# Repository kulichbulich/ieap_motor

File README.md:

# 4-Channel Motor Controller with ESP32
## Parts

### ESP32
Pin assigment https://github.com/atomic14/esp32-s3-pinouts/blob/main/README.md?utm_source=chatgpt.com

### Motor-driver module
Datasheet: https://www.analog.com/media/en/technical-documentation/data-sheets/TMC2209-BOB_datasheet_rev1.00.pdf
Motor module (KiCAD files): https://www.analog.com/media/en/evaluation-documentation/evaluation-design-files/TMC2209-BOB_Rev1.0.zip

### DC/DC converter
LT8610: https://www.analog.com/media/en/technical-documentation/data-sheets/lt8610.pdf
+5V Power supply

+5V Power supply

### Polyswitch
https://cz.mouser.com/ProductDetail/Littelfuse/MINISMDC150F-24-2?qs=F6FIpiMdEVZ%2Fp37J%2FDHAxA%3D%3D

# Enclosure

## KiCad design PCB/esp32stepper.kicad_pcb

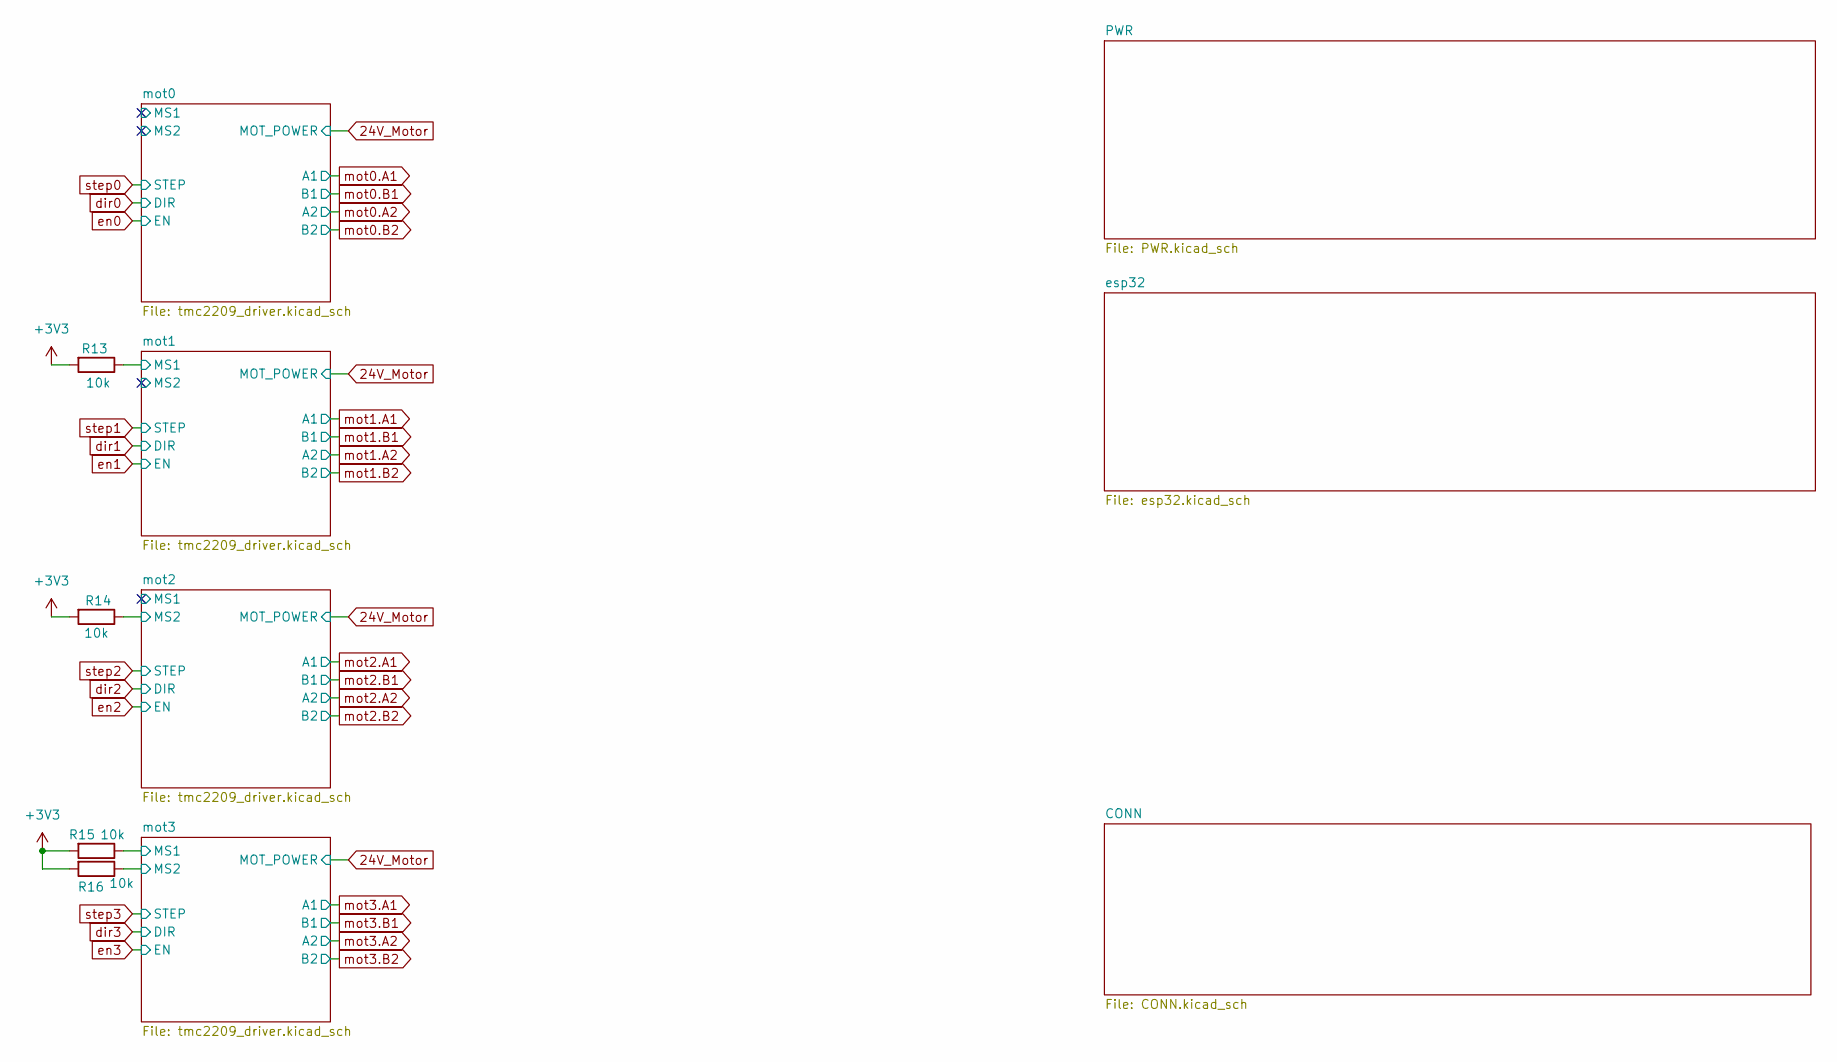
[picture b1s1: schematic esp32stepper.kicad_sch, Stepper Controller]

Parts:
R13, R14, R15, R16: 10k; R_0603_1608Metric_Pad0.98x0.95mm_HandSolder

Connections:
+3V3: R13.2, R14.2, R15.2, R16.2; also elsewhere on the board
/mot1/MS1: R13.1; also elsewhere on the board
/mot2/MS2: R14.1; also elsewhere on the board
/mot3/MS1: R15.1; also elsewhere on the board
/mot3/MS2: R16.1; also elsewhere on the board

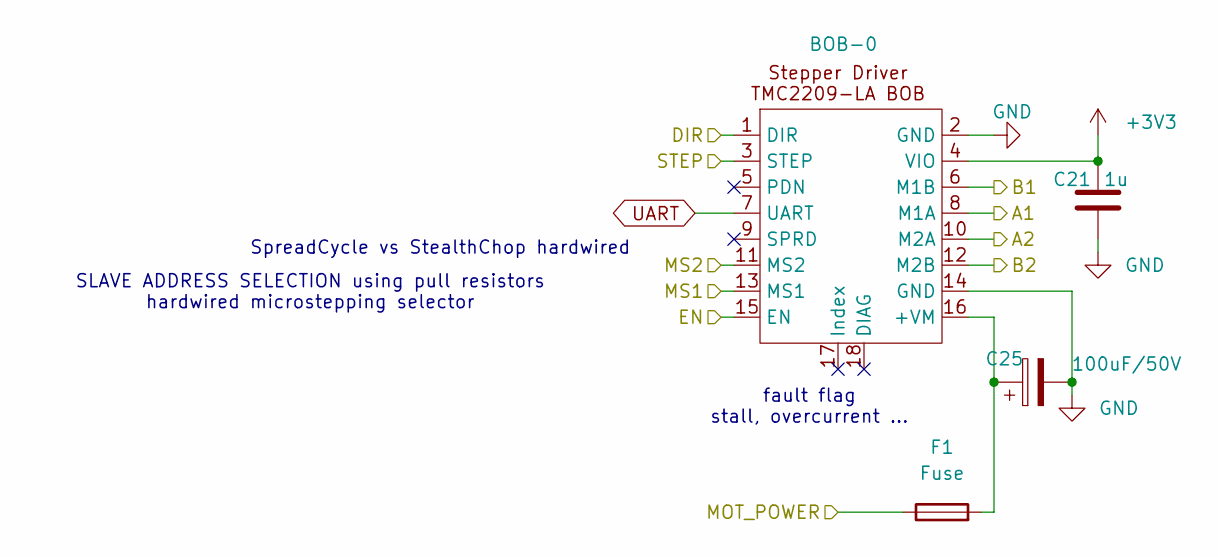
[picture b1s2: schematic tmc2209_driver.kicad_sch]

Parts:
BOB-0: TMC2209_SilentStepStick
C21: 1u; C_0603_1608Metric_Pad1.08x0.95mm_HandSolder
C25: 100uF/50V; CP_Elec_8x10.5
F1: Fuse; Fuse_1812_4532Metric_Pad1.30x3.40mm_HandSolder

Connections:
24V_Motor: F1.1; also elsewhere on the board
+3V3: BOB-0.4 (VIO), C21.2; also elsewhere on the board
/mot0/MS1: BOB-0.13 (MS1)
/mot0/MS2: BOB-0.11 (MS2)
GND: BOB-0.2 (GND), BOB-0.14 (GND), C21.1, C25.2; also elsewhere on the board
unnamed: BOB-0.16 (+VM), C25.1, F1.2
UART: BOB-0.7 (UART); also elsewhere on the board
dir0: BOB-0.1 (DIR); also elsewhere on the board
en0: BOB-0.15 (EN); also elsewhere on the board
mot0.A1: BOB-0.8 (M1A); also elsewhere on the board
mot0.A2: BOB-0.10 (M2A); also elsewhere on the board
mot0.B1: BOB-0.6 (M1B); also elsewhere on the board
mot0.B2: BOB-0.12 (M2B); also elsewhere on the board
step0: BOB-0.3 (STEP); also elsewhere on the board

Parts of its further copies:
C22, C23, C24: 1u; C_0603_1608Metric_Pad1.08x0.95mm_HandSolder
C26, C27, C28: 100uF/50V; CP_Elec_8x10.5
F3, F4, F5: Fuse; Fuse_1812_4532Metric_Pad1.30x3.40mm_HandSolder

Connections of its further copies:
24V_Motor: F3.1, F4.1, F5.1; also elsewhere on the board
+3V3: C22.2, C23.2, C24.2; also elsewhere on the board
GND: C22.1, C23.1, C24.1, C26.2, C27.2, C28.2; also elsewhere on the board
unnamed 17: C26.1, F3.2; also elsewhere on the board
unnamed 18: C27.1, F4.2; also elsewhere on the board
unnamed 19: C28.1, F5.2; also elsewhere on the board

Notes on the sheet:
fault flag stall, overcurrent ...
SLAVE ADDRESS SELECTION using pull resistors hardwired microstepping selector
SpreadCycle vs StealthChop hardwired

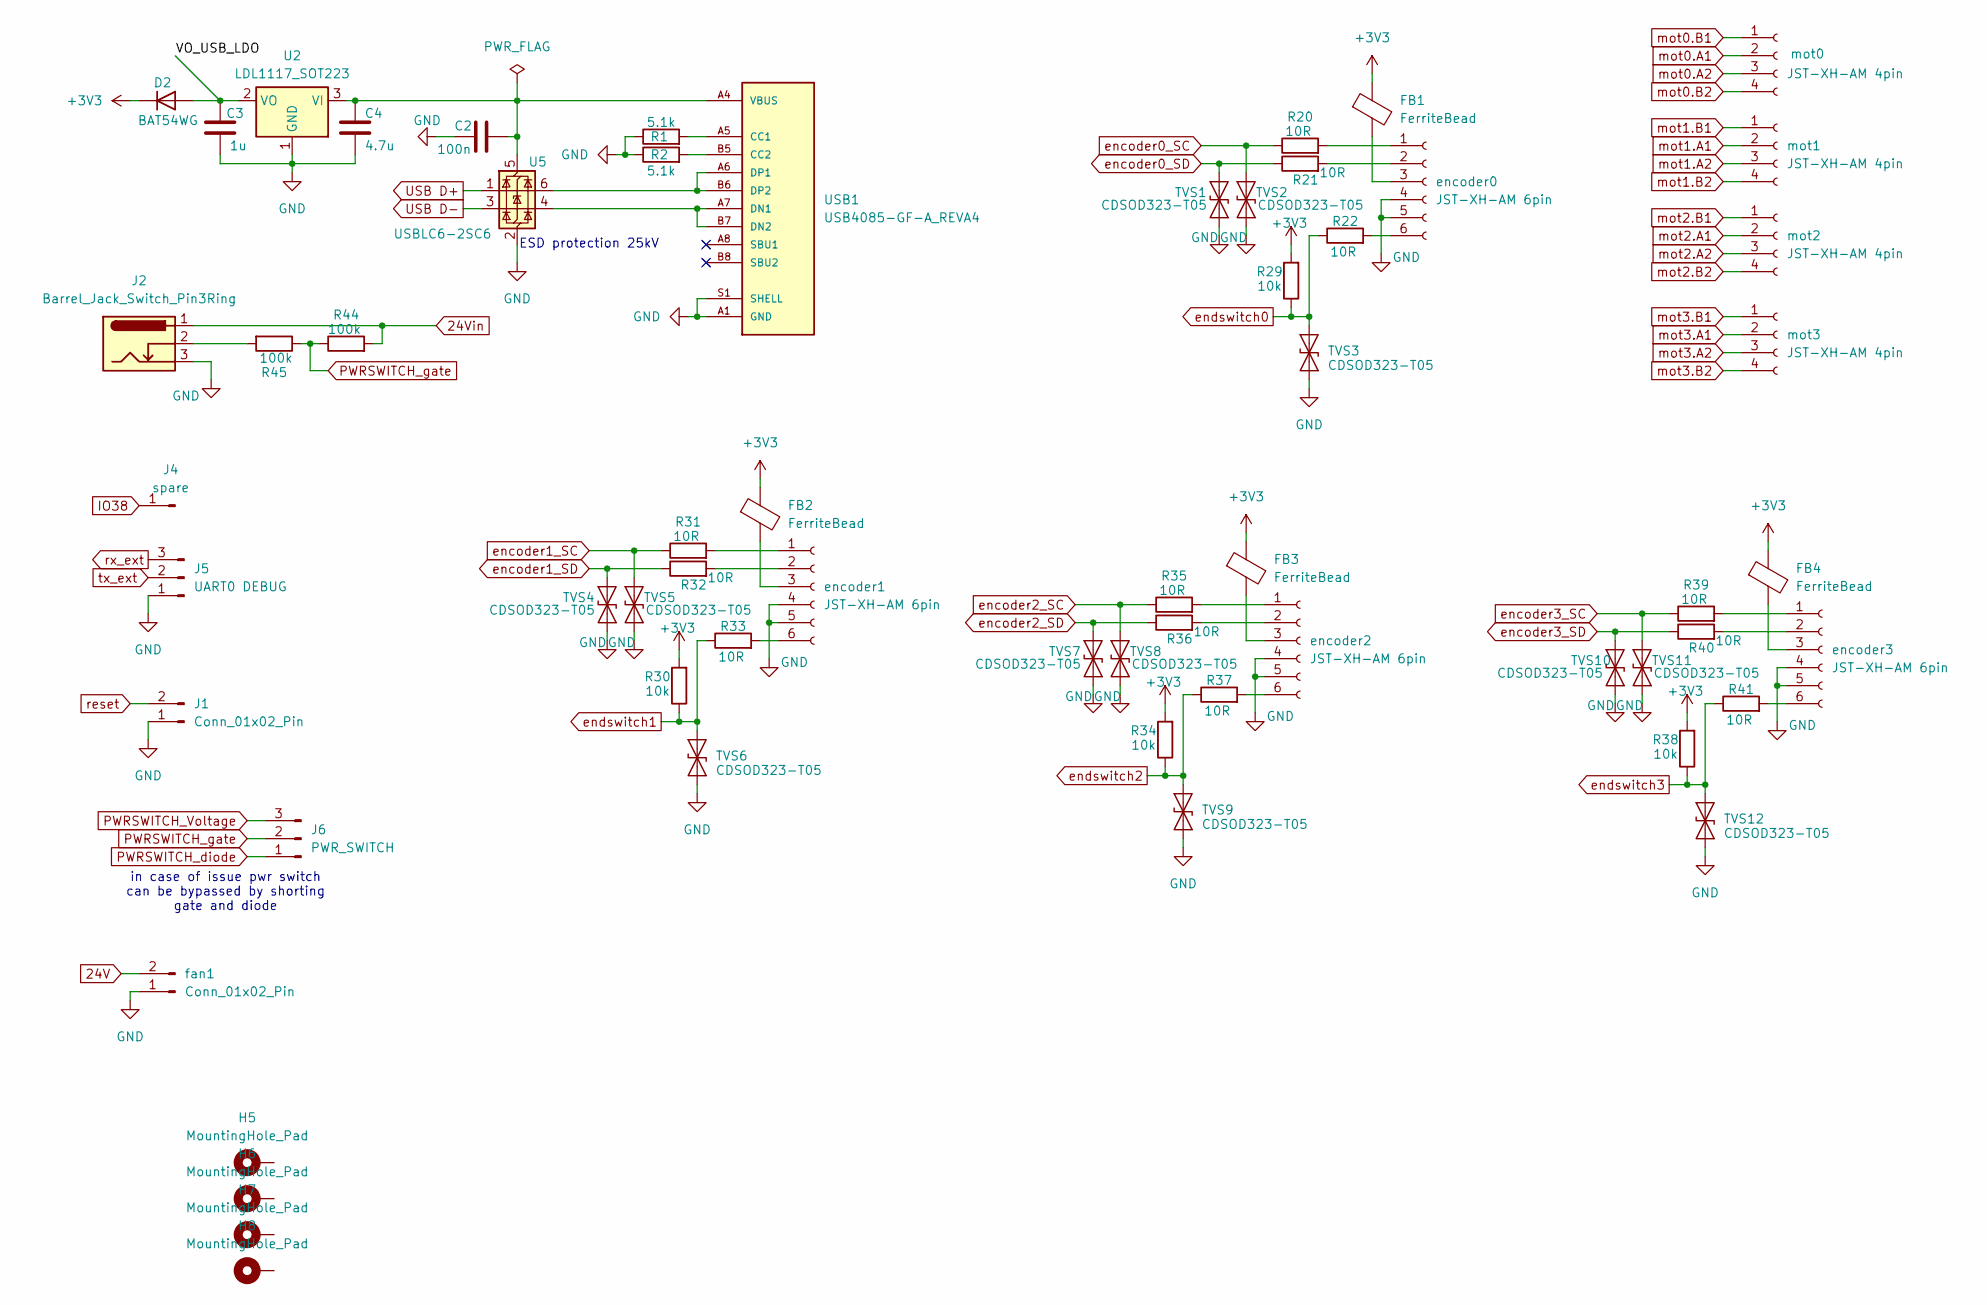
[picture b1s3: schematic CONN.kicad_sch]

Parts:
C2: 100n; C_0603_1608Metric_Pad1.08x0.95mm_HandSolder
C3: 1u; C_0603_1608Metric_Pad1.08x0.95mm_HandSolder
C4: 4.7u; C_0603_1608Metric_Pad1.08x0.95mm_HandSolder
D2: BAT54WG; SOT-323_SC-70_Handsoldering
FB1, FB2, FB3, FB4: FerriteBead; L_0603_1608Metric_Pad1.05x0.95mm_HandSolder
H5, H6, H7, H8: MountingHole_Pad; MountingHole_3.2mm_M3_DIN965_Pad
J1: Conn_01x02_Pin; PinHeader_1x02_P2.54mm_Vertical
J2: Barrel_Jack_Switch_Pin3Ring; BarrelJack_Wuerth_6941xx301002
J4: spare; PinHeader_1x01_P2.54mm_Vertical
J5: UART0 DEBUG; PinHeader_1x03_P2.54mm_Vertical
J6: PWR_SWITCH; PinHeader_1x03_P2.54mm_Vertical
R1, R2: 5.1k; R_0603_1608Metric_Pad0.98x0.95mm_HandSolder
R20, R21, R22, R31, R32, R33, R35, R36, R37, R39, R40, R41: 10R; R_0603_1608Metric_Pad0.98x0.95mm_HandSolder
R29, R30, R34, R38: 10k; R_0603_1608Metric_Pad0.98x0.95mm_HandSolder
R44, R45: 100k; R_0603_1608Metric_Pad0.98x0.95mm_HandSolder
TVS1, TVS2, TVS3, TVS4, TVS5, TVS6, TVS7, TVS8, TVS9, TVS10, TVS11, TVS12: CDSOD323-T05; D_SOD-323
U2: LDL1117_SOT223; SOT-223-3_TabPin2
U5: USBLC6-2SC6; SOT-23-6
USB1: USB4085-GF-A_REVA4; GCT_USB4085-GF-A_REVA4; PARTREV A4
encoder0, encoder1, encoder2, encoder3: JST-XH-AM 6pin; JST_XH_B6B-XH-AM_1x06_P2.50mm_Vertical
fan1: Conn_01x02_Pin; PinHeader_1x02_P2.54mm_Vertical
mot0, mot1, mot2, mot3: JST-XH-AM 4pin; JST_XH_B4B-XH-AM_1x04_P2.50mm_Vertical

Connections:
24V: fan1.2; also elsewhere on the board
24Vin: J2.1, R44.2; also elsewhere on the board
+3V3: D2.1 (K), FB1.1, FB2.1, FB3.1, FB4.1, R29.2, R30.2, R34.2, R38.2; also elsewhere on the board
/CONN/VO_USB_LDO: C3.1, D2.2 (A), U2.2 (VO)
GND: C2.1, C3.2, C4.2, J1.1, J2.3, J5.1, R1.1, R2.1, TVS1.1 (A1), TVS2.1 (A1), TVS3.1 (A1), TVS4.1 (A1), TVS5.1 (A1), TVS6.1 (A1), TVS7.1 (A1), TVS8.1 (A1), TVS9.1 (A1), TVS10.1 (A1), TVS11.1 (A1), TVS12.1 (A1), U2.1 (GND), U5.2 (GND), USB1.A1 (GND), USB1.A12 (GND), USB1.B1 (GND), USB1.B12 (GND), USB1.S1 (SHELL), USB1.S2 (SHELL), USB1.S3 (SHELL), USB1.S4 (SHELL), encoder0.4, encoder0.5, encoder1.4, encoder1.5, encoder2.4, encoder2.5, encoder3.4, encoder3.5, fan1.1; also elsewhere on the board
IO38: J4.1 (Pin_1_1); also elsewhere on the board
unnamed: J2.2, R45.2
unnamed: R1.2, USB1.A5 (CC1)
unnamed: R2.2, USB1.B5 (CC2)
unnamed: U5.4 (I/O2), USB1.A7 (DN1), USB1.B7 (DN2)
unnamed: U5.6 (I/O1), USB1.A6 (DP1), USB1.B6 (DP2)
unnamed: R20.2, encoder0.1
unnamed: R21.2, encoder0.2
unnamed: FB1.2, encoder0.3
unnamed: R22.2, encoder0.6
unnamed: R31.2, encoder1.1
unnamed: R32.2, encoder1.2
unnamed: FB2.2, encoder1.3
unnamed: R33.2, encoder1.6
unnamed: R35.2, encoder2.1
unnamed: R36.2, encoder2.2
unnamed: FB3.2, encoder2.3
unnamed: R37.2, encoder2.6
unnamed: R39.2, encoder3.1
unnamed: R40.2, encoder3.2
unnamed: FB4.2, encoder3.3
unnamed: R41.2, encoder3.6
PWRSWITCH_Voltage: J6.3; also elsewhere on the board
PWRSWITCH_diode: J6.1; also elsewhere on the board
PWRSWITCH_gate: J6.2, R44.1, R45.1; also elsewhere on the board
USB D+: U5.1 (I/O1); also elsewhere on the board
USB D-: U5.3 (I/O2); also elsewhere on the board
VBUS: C2.2, C4.1, U2.3 (VI), U5.5 (VBUS), USB1.A4 (VBUS), USB1.A9 (VBUS), USB1.B4 (VBUS), USB1.B9 (VBUS)
encoder0_SC: R20.1, TVS2.2 (A2); also elsewhere on the board
encoder0_SD: R21.1, TVS1.2 (A2); also elsewhere on the board
encoder1_SC: R31.1, TVS5.2 (A2); also elsewhere on the board
encoder1_SD: R32.1, TVS4.2 (A2); also elsewhere on the board
encoder2_SC: R35.1, TVS8.2 (A2); also elsewhere on the board
encoder2_SD: R36.1, TVS7.2 (A2); also elsewhere on the board
encoder3_SC: R39.1, TVS11.2 (A2); also elsewhere on the board
encoder3_SD: R40.1, TVS10.2 (A2); also elsewhere on the board
endswitch0: R22.1, R29.1, TVS3.2 (A2); also elsewhere on the board
endswitch1: R30.1, R33.1, TVS6.2 (A2); also elsewhere on the board
endswitch2: R34.1, R37.1, TVS9.2 (A2); also elsewhere on the board
endswitch3: R38.1, R41.1, TVS12.2 (A2); also elsewhere on the board
mot0.A1: mot0.2; also elsewhere on the board
mot0.A2: mot0.3; also elsewhere on the board
mot0.B1: mot0.1; also elsewhere on the board
mot0.B2: mot0.4; also elsewhere on the board
mot1.A1: mot1.2; also elsewhere on the board
mot1.A2: mot1.3; also elsewhere on the board
mot1.B1: mot1.1; also elsewhere on the board
mot1.B2: mot1.4; also elsewhere on the board
mot2.A1: mot2.2; also elsewhere on the board
mot2.A2: mot2.3; also elsewhere on the board
mot2.B1: mot2.1; also elsewhere on the board
mot2.B2: mot2.4; also elsewhere on the board
mot3.A1: mot3.2; also elsewhere on the board
mot3.A2: mot3.3; also elsewhere on the board
mot3.B1: mot3.1; also elsewhere on the board
mot3.B2: mot3.4; also elsewhere on the board
reset: J1.2; also elsewhere on the board
rx_ext: J5.3; also elsewhere on the board
tx_ext: J5.2; also elsewhere on the board

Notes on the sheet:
in case of issue pwr switch can be bypassed by shorting gate and diode
ESD protection 25kV

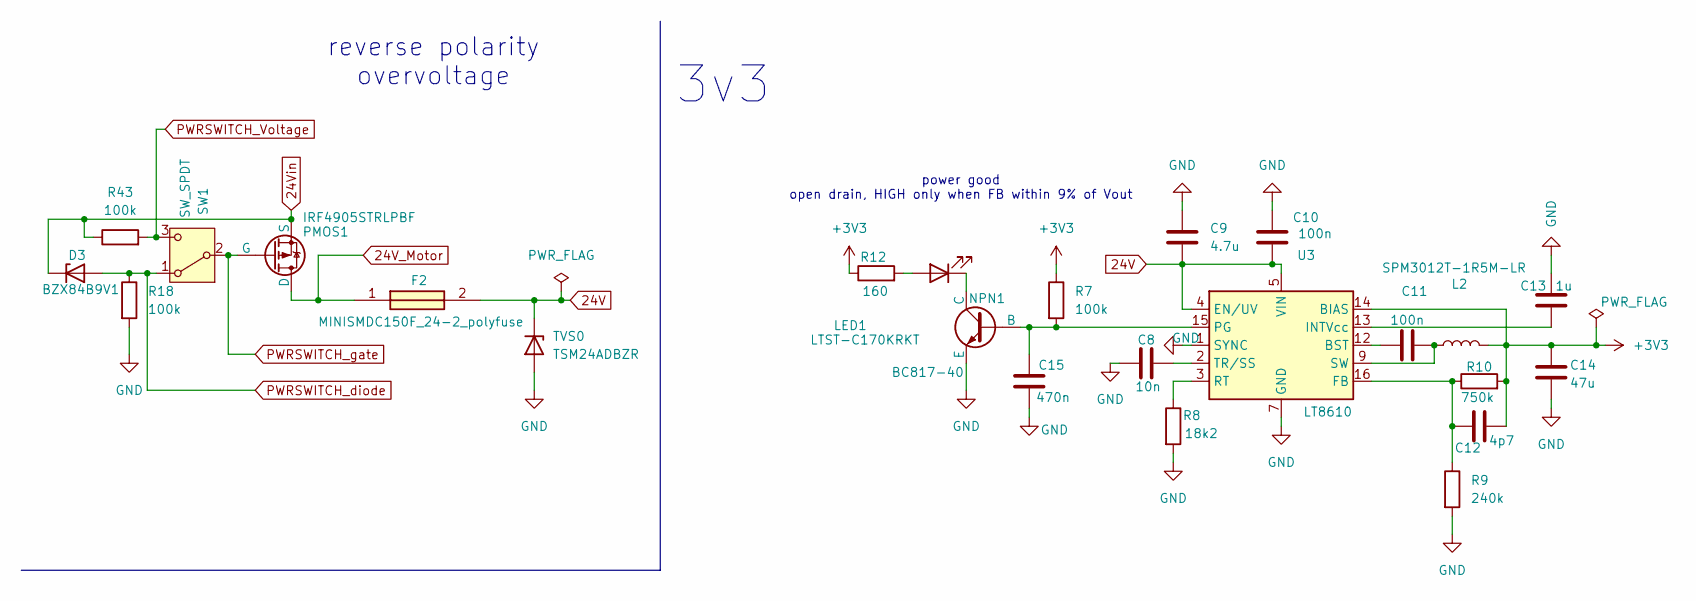
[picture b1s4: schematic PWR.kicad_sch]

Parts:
C8: 10n; C_0603_1608Metric_Pad1.08x0.95mm_HandSolder
C9: 4.7u; C_0805_2012Metric_Pad1.18x1.45mm_HandSolder
C10, C11: 100n; C_0603_1608Metric_Pad1.08x0.95mm_HandSolder
C12: 4p7; C_0603_1608Metric_Pad1.08x0.95mm_HandSolder
C13: 1u; C_0603_1608Metric_Pad1.08x0.95mm_HandSolder
C14: 47u; C_0603_1608Metric_Pad1.08x0.95mm_HandSolder
C15: 470n; C_0603_1608Metric_Pad1.08x0.95mm_HandSolder
D3: BZX84B9V1; SOT-23
F2: MINISMDC150F_24-2_polyfuse; polyfuse; Mouser Part Number 650-MINISMDC150F/24
L2: SPM3012T-1R5M-LR; SPM3010-3020
LED1: LTST-C170KRKT; LED_0805_2012Metric_Pad1.15x1.40mm_HandSolder
NPN1: BC817-40; TSOT-23_HandSoldering
PMOS1: IRF4905STRLPBF; TO-263-2
R7, R18, R43: 100k; R_0603_1608Metric_Pad0.98x0.95mm_HandSolder
R8: 18k2; R_0603_1608Metric_Pad0.98x0.95mm_HandSolder
R9: 240k; R_0603_1608Metric_Pad0.98x0.95mm_HandSolder
R10: 750k; R_0603_1608Metric_Pad0.98x0.95mm_HandSolder
R12: 160; R_0603_1608Metric_Pad0.98x0.95mm_HandSolder
SW1: SW_SPDT
TVS0: TSM24ADBZR; TSOT-23
U3: LT8610; MSOP-16-1EP_3x4.039mm_P0.5mm_EP1.651x2.845mm_ThermalVias

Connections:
24V: C9.2, C10.2, F2.2, TVS0.1 (K), U3.4 (EN/UV), U3.5 (VIN), U3.6 (VIN); also elsewhere on the board
24V_Motor: F2.1, PMOS1.1 (D); also elsewhere on the board
24Vin: D3.1 (K), PMOS1.3 (S), R43.1; also elsewhere on the board
+3V3: C12.1, C14.1, L2.2, R7.1, R10.2, R12.1, U3.14 (BIAS); also elsewhere on the board
GND: C8.1, C9.1, C10.1, C13.2, C14.2, C15.1, NPN1.3 (E), R8.2, R9.2, R18.2, TVS0.2 (A), U3.1 (SYNC), U3.7 (GND), U3.8 (GND), U3.17 (GND); also elsewhere on the board
unnamed: C11.2, L2.1, U3.9 (SW), U3.10 (SW), U3.11 (SW)
unnamed: LED1.2 (A), R12.2
unnamed: LED1.1 (K), NPN1.1 (C)
unnamed: C15.2, NPN1.2 (B), R7.2, U3.15 (PG)
unnamed: C11.1, U3.12 (BST)
unnamed: C12.2, R9.1, R10.1, U3.16 (FB)
unnamed: C13.1, U3.13 (INTVcc)
unnamed: R8.1, U3.3 (RT)
unnamed: C8.2, U3.2 (TR/SS)
PWRSWITCH_Voltage: R43.2, SW1.3 (C); also elsewhere on the board
PWRSWITCH_diode: D3.2 (A), R18.1, SW1.1 (A); also elsewhere on the board
PWRSWITCH_gate: PMOS1.2 (G), SW1.2 (B); also elsewhere on the board

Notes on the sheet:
power good open drain, HIGH only when FB within 9% of Vout
reverse polarity overvoltage
3v3

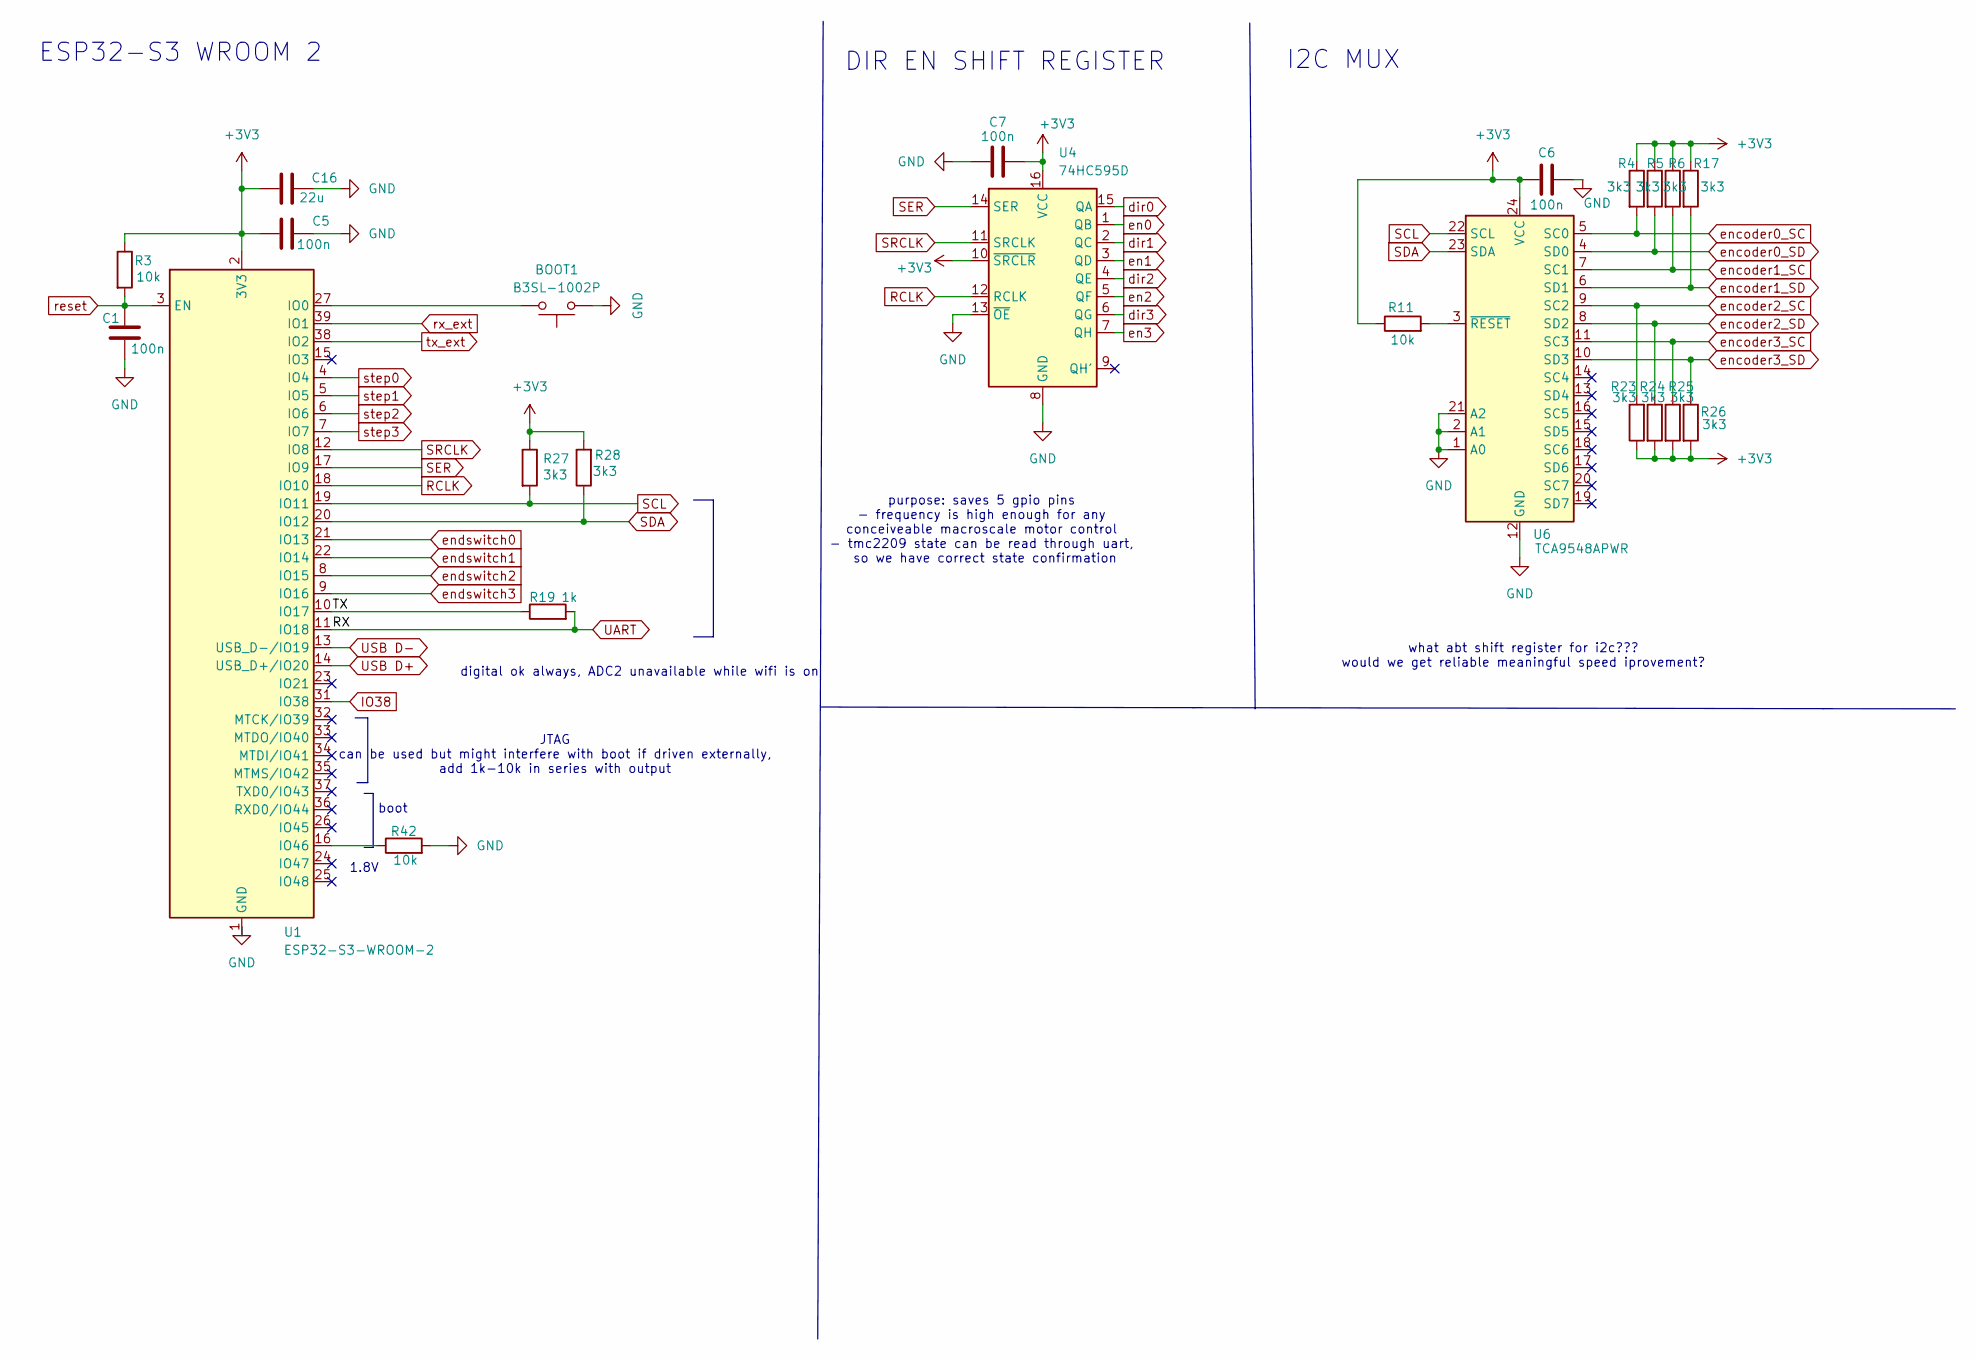
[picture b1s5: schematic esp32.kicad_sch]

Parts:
BOOT1: B3SL-1002P; SW_SPST_B3SL-1002P
C1, C5, C6, C7: 100n; C_0603_1608Metric_Pad1.08x0.95mm_HandSolder
C16: 22u; C_0603_1608Metric_Pad1.08x0.95mm_HandSolder
R3, R11, R42: 10k; R_0603_1608Metric_Pad0.98x0.95mm_HandSolder
R4, R5, R6, R17, R23, R24, R25, R26, R27, R28: 3k3; R_0603_1608Metric_Pad0.98x0.95mm_HandSolder
R19: 1k; R_0603_1608Metric_Pad0.98x0.95mm_HandSolder
U1: ESP32-S3-WROOM-2
U4: 74HC595D; SOIC-16_3.9x9.9mm_P1.27mm
U6: TCA9548APWR; TSSOP-24_4.4x7.8mm_P0.65mm

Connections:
+3V3: C5.1, C6.1, C7.2, C16.2, R3.1, R4.1, R5.1, R6.1, R11.1, R17.1, R23.1, R24.2, R25.2, R26.2, R27.1, R28.2, U1.2 (3V3), U4.10 (~SRCLR), U4.16 (VCC), U6.24 (VCC); also elsewhere on the board
/esp32/TX: R19.1, U1.10 (IO17)
GND: BOOT1.1, C1.2, C5.2, C6.2, C7.1, C16.1, R42.2, U1.1 (GND), U1.40 (GND), U1.41 (GND), U4.8 (GND), U4.13 (~OE), U6.1 (A0), U6.2 (A1), U6.12 (GND), U6.21 (A2); also elsewhere on the board
IO38: U1.31 (IO38); also elsewhere on the board
unnamed: BOOT1.2, U1.27 (IO0)
unnamed: R42.1, U1.16 (IO46)
unnamed: R11.2, U6.3 (~RESET)
RCLK: U1.18 (IO10), U4.12 (RCLK)
SCL: R27.2, U1.19 (IO11), U6.22 (SCL)
SDA: R28.1, U1.20 (IO12), U6.23 (SDA)
SER: U1.17 (IO9), U4.14 (SER)
SRCLK: U1.12 (IO8), U4.11 (SRCLK)
UART: R19.2, U1.11 (IO18); also elsewhere on the board
USB D+: U1.14 (USB_D+/IO20); also elsewhere on the board
USB D-: U1.13 (USB_D-/IO19); also elsewhere on the board
dir0: U4.15 (QA); also elsewhere on the board
dir1: U4.2 (QC); also elsewhere on the board
dir2: U4.4 (QE); also elsewhere on the board
dir3: U4.6 (QG); also elsewhere on the board
en0: U4.1 (QB); also elsewhere on the board
en1: U4.3 (QD); also elsewhere on the board
en2: U4.5 (QF); also elsewhere on the board
en3: U4.7 (QH); also elsewhere on the board
encoder0_SC: R4.2, U6.5 (SC0); also elsewhere on the board
encoder0_SD: R5.2, U6.4 (SD0); also elsewhere on the board
encoder1_SC: R6.2, U6.7 (SC1); also elsewhere on the board
encoder1_SD: R17.2, U6.6 (SD1); also elsewhere on the board
encoder2_SC: R23.2, U6.9 (SC2); also elsewhere on the board
encoder2_SD: R24.1, U6.8 (SD2); also elsewhere on the board
encoder3_SC: R25.1, U6.11 (SC3); also elsewhere on the board
encoder3_SD: R26.1, U6.10 (SD3); also elsewhere on the board
endswitch0: U1.21 (IO13); also elsewhere on the board
endswitch1: U1.22 (IO14); also elsewhere on the board
endswitch2: U1.8 (IO15); also elsewhere on the board
endswitch3: U1.9 (IO16); also elsewhere on the board
reset: C1.1, R3.2, U1.3 (EN); also elsewhere on the board
rx_ext: U1.39 (IO1); also elsewhere on the board
step0: U1.4 (IO4); also elsewhere on the board
step1: U1.5 (IO5); also elsewhere on the board
step2: U1.6 (IO6); also elsewhere on the board
step3: U1.7 (IO7); also elsewhere on the board
tx_ext: U1.38 (IO2); also elsewhere on the board

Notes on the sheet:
purpose: saves 5 gpio pins - frequency is high enough for any conceiveable macroscale motor control - tmc2209 state can be read through uart, so we have correct state confirmation
JTAG can be used but might interfere with boot if driven externally, add 1k-10k in series with output
digital ok always, ADC2 unavailable while wifi is on
boot
I2C MUX
DIR EN SHIFT REGISTER
what abt shift register for i2c??? would we get reliable meaningful speed iprovement?
1.8V
ESP32-S3 WROOM 2

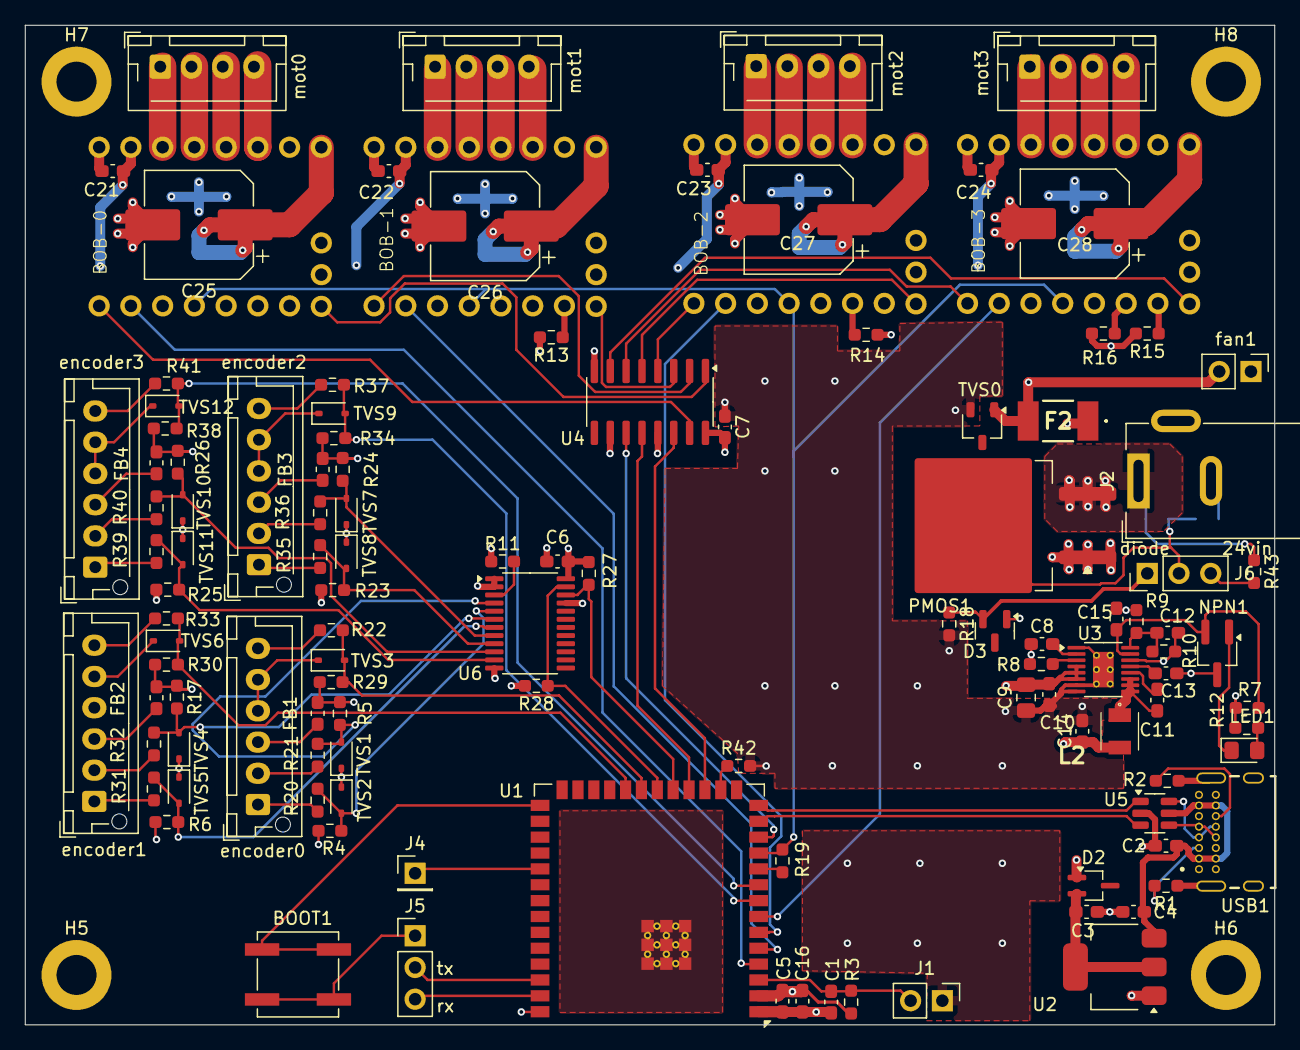
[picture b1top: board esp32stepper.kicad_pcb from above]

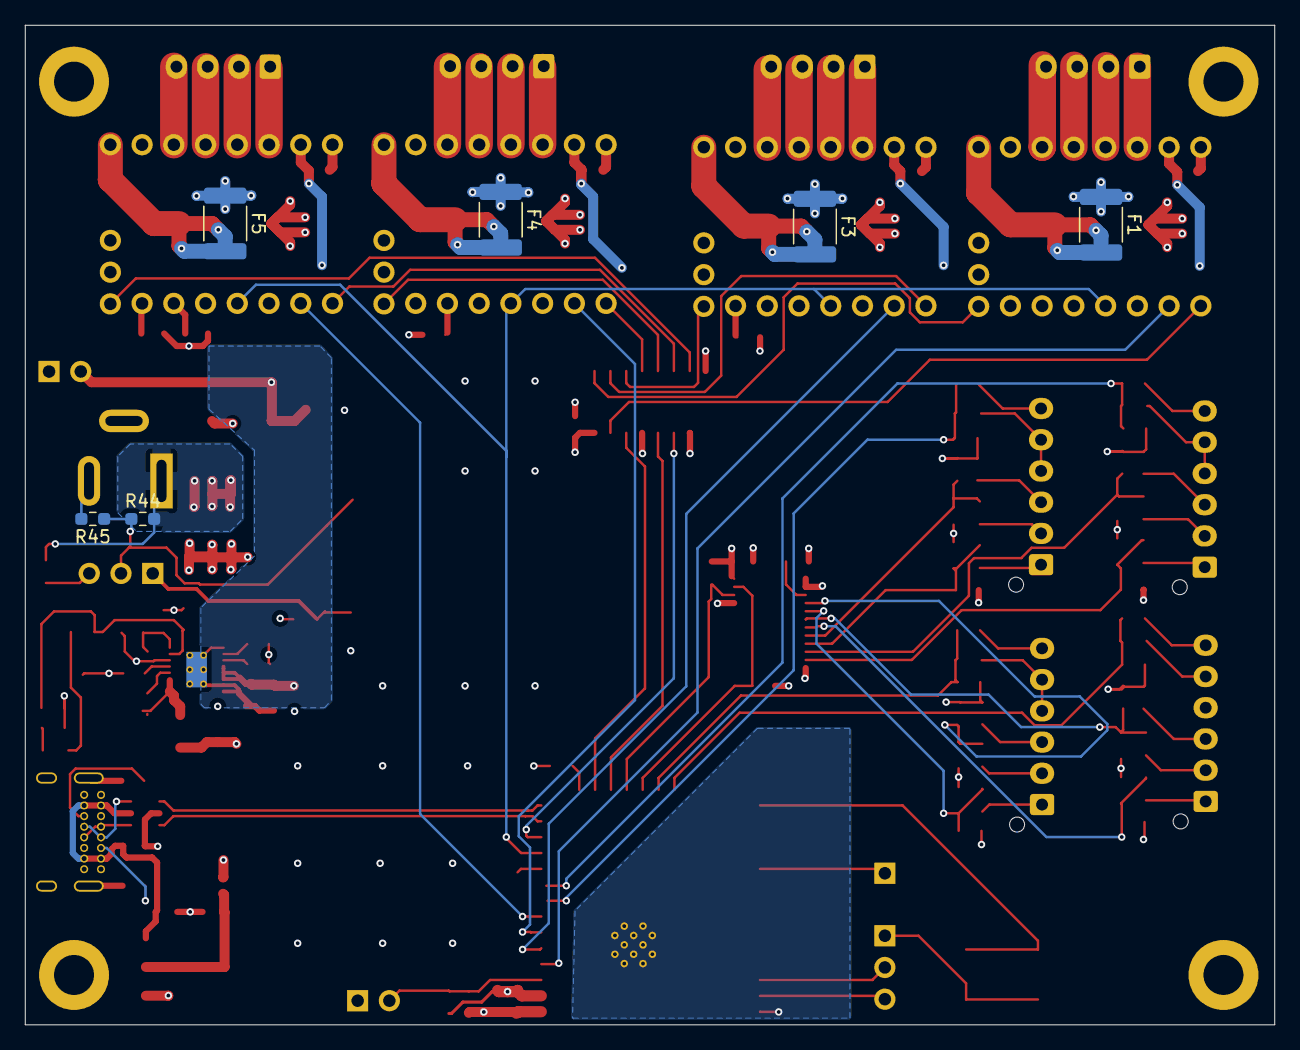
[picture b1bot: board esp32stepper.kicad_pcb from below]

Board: 4 copper layers, 100.0 x 80.0 mm, 127 parts (6 on the bottom side), 104 nets.

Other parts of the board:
BOB-1, BOB-2, BOB-3: TMC2209_SilentStepStick

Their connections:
+3V3: BOB-1.4 (VIO), BOB-2.4 (VIO), BOB-3.4 (VIO); also elsewhere on the board
/mot1/MS1: BOB-1.13 (MS1); also elsewhere on the board
/mot2/MS2: BOB-2.11 (MS2); also elsewhere on the board
/mot3/MS1: BOB-3.13 (MS1); also elsewhere on the board
/mot3/MS2: BOB-3.11 (MS2); also elsewhere on the board
GND: BOB-1.2 (GND), BOB-1.14 (GND), BOB-2.2 (GND), BOB-2.14 (GND), BOB-3.2 (GND), BOB-3.14 (GND); also elsewhere on the board
unnamed 17: BOB-1.16 (+VM); also elsewhere on the board
unnamed 18: BOB-2.16 (+VM); also elsewhere on the board
unnamed 19: BOB-3.16 (+VM); also elsewhere on the board
UART: BOB-1.7 (UART), BOB-2.7 (UART), BOB-3.7 (UART); also elsewhere on the board
dir1: BOB-1.1 (DIR); also elsewhere on the board
dir2: BOB-2.1 (DIR); also elsewhere on the board
dir3: BOB-3.1 (DIR); also elsewhere on the board
en1: BOB-1.15 (EN); also elsewhere on the board
en2: BOB-2.15 (EN); also elsewhere on the board
en3: BOB-3.15 (EN); also elsewhere on the board
mot1.A1: BOB-1.8 (M1A); also elsewhere on the board
mot1.A2: BOB-1.10 (M2A); also elsewhere on the board
mot1.B1: BOB-1.6 (M1B); also elsewhere on the board
mot1.B2: BOB-1.12 (M2B); also elsewhere on the board
mot2.A1: BOB-2.8 (M1A); also elsewhere on the board
mot2.A2: BOB-2.10 (M2A); also elsewhere on the board
mot2.B1: BOB-2.6 (M1B); also elsewhere on the board
mot2.B2: BOB-2.12 (M2B); also elsewhere on the board
mot3.A1: BOB-3.8 (M1A); also elsewhere on the board
mot3.A2: BOB-3.10 (M2A); also elsewhere on the board
mot3.B1: BOB-3.6 (M1B); also elsewhere on the board
mot3.B2: BOB-3.12 (M2B); also elsewhere on the board
step1: BOB-1.3 (STEP); also elsewhere on the board
step2: BOB-2.3 (STEP); also elsewhere on the board
step3: BOB-3.3 (STEP); also elsewhere on the board

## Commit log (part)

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2026-06-17 [upd] Schematic
2026-06-29 initial commit esp32stepper
2026-06-29 [upd] Reorganization
2026-06-29 [doc] Basic documents
2026-06-29 [doc] New module driver
2026-06-30 revision 1: I2C pullups, USB LDO, etc.
